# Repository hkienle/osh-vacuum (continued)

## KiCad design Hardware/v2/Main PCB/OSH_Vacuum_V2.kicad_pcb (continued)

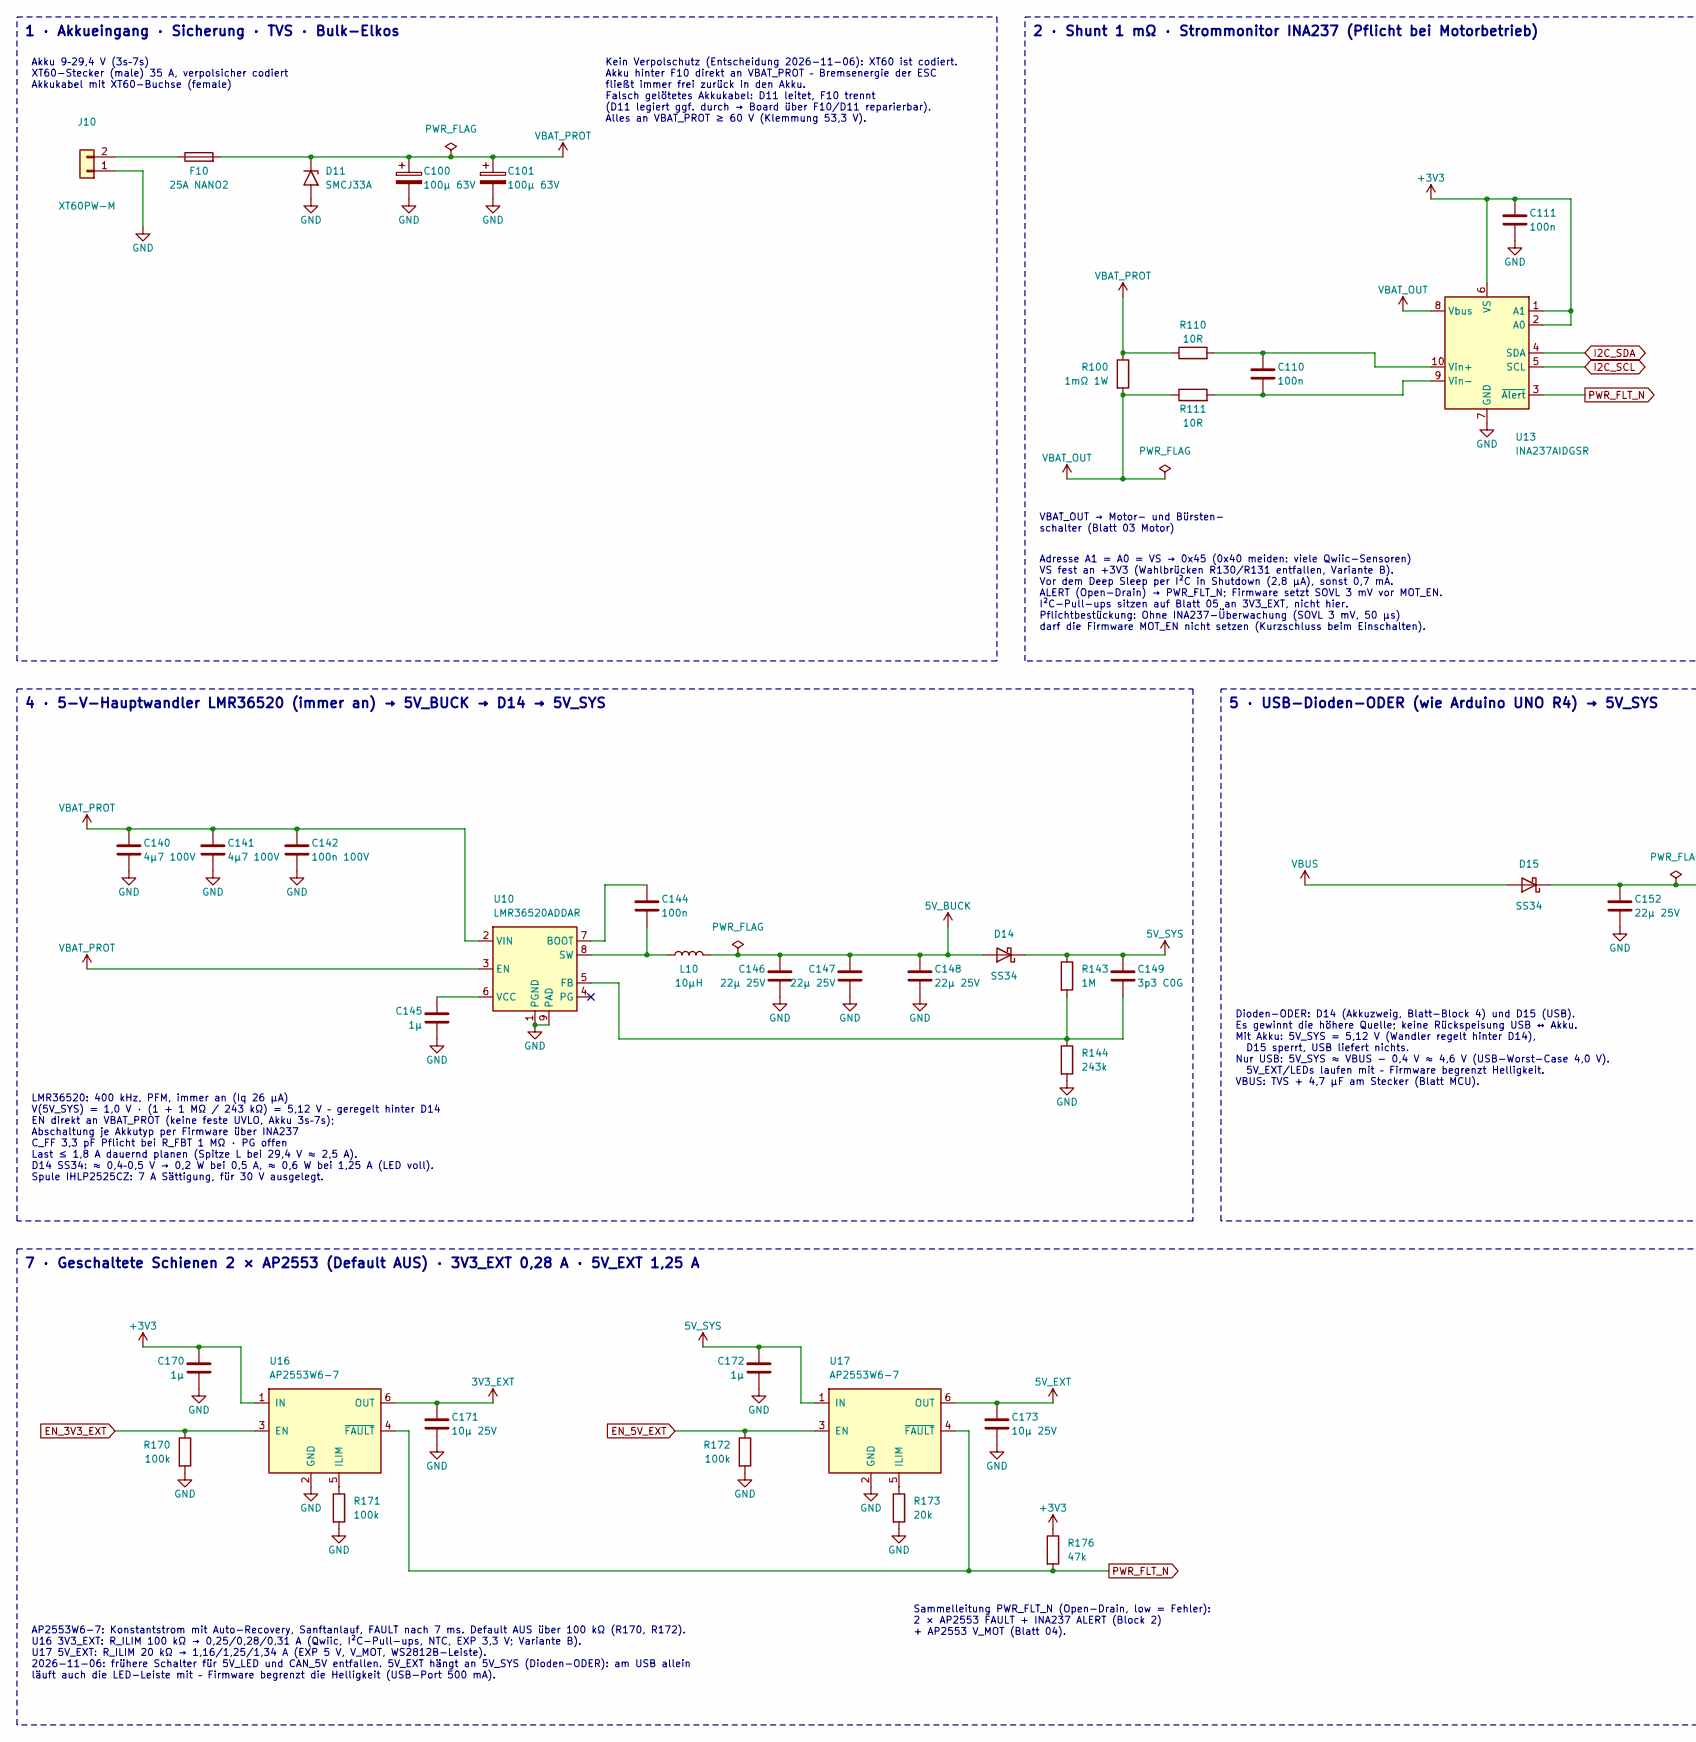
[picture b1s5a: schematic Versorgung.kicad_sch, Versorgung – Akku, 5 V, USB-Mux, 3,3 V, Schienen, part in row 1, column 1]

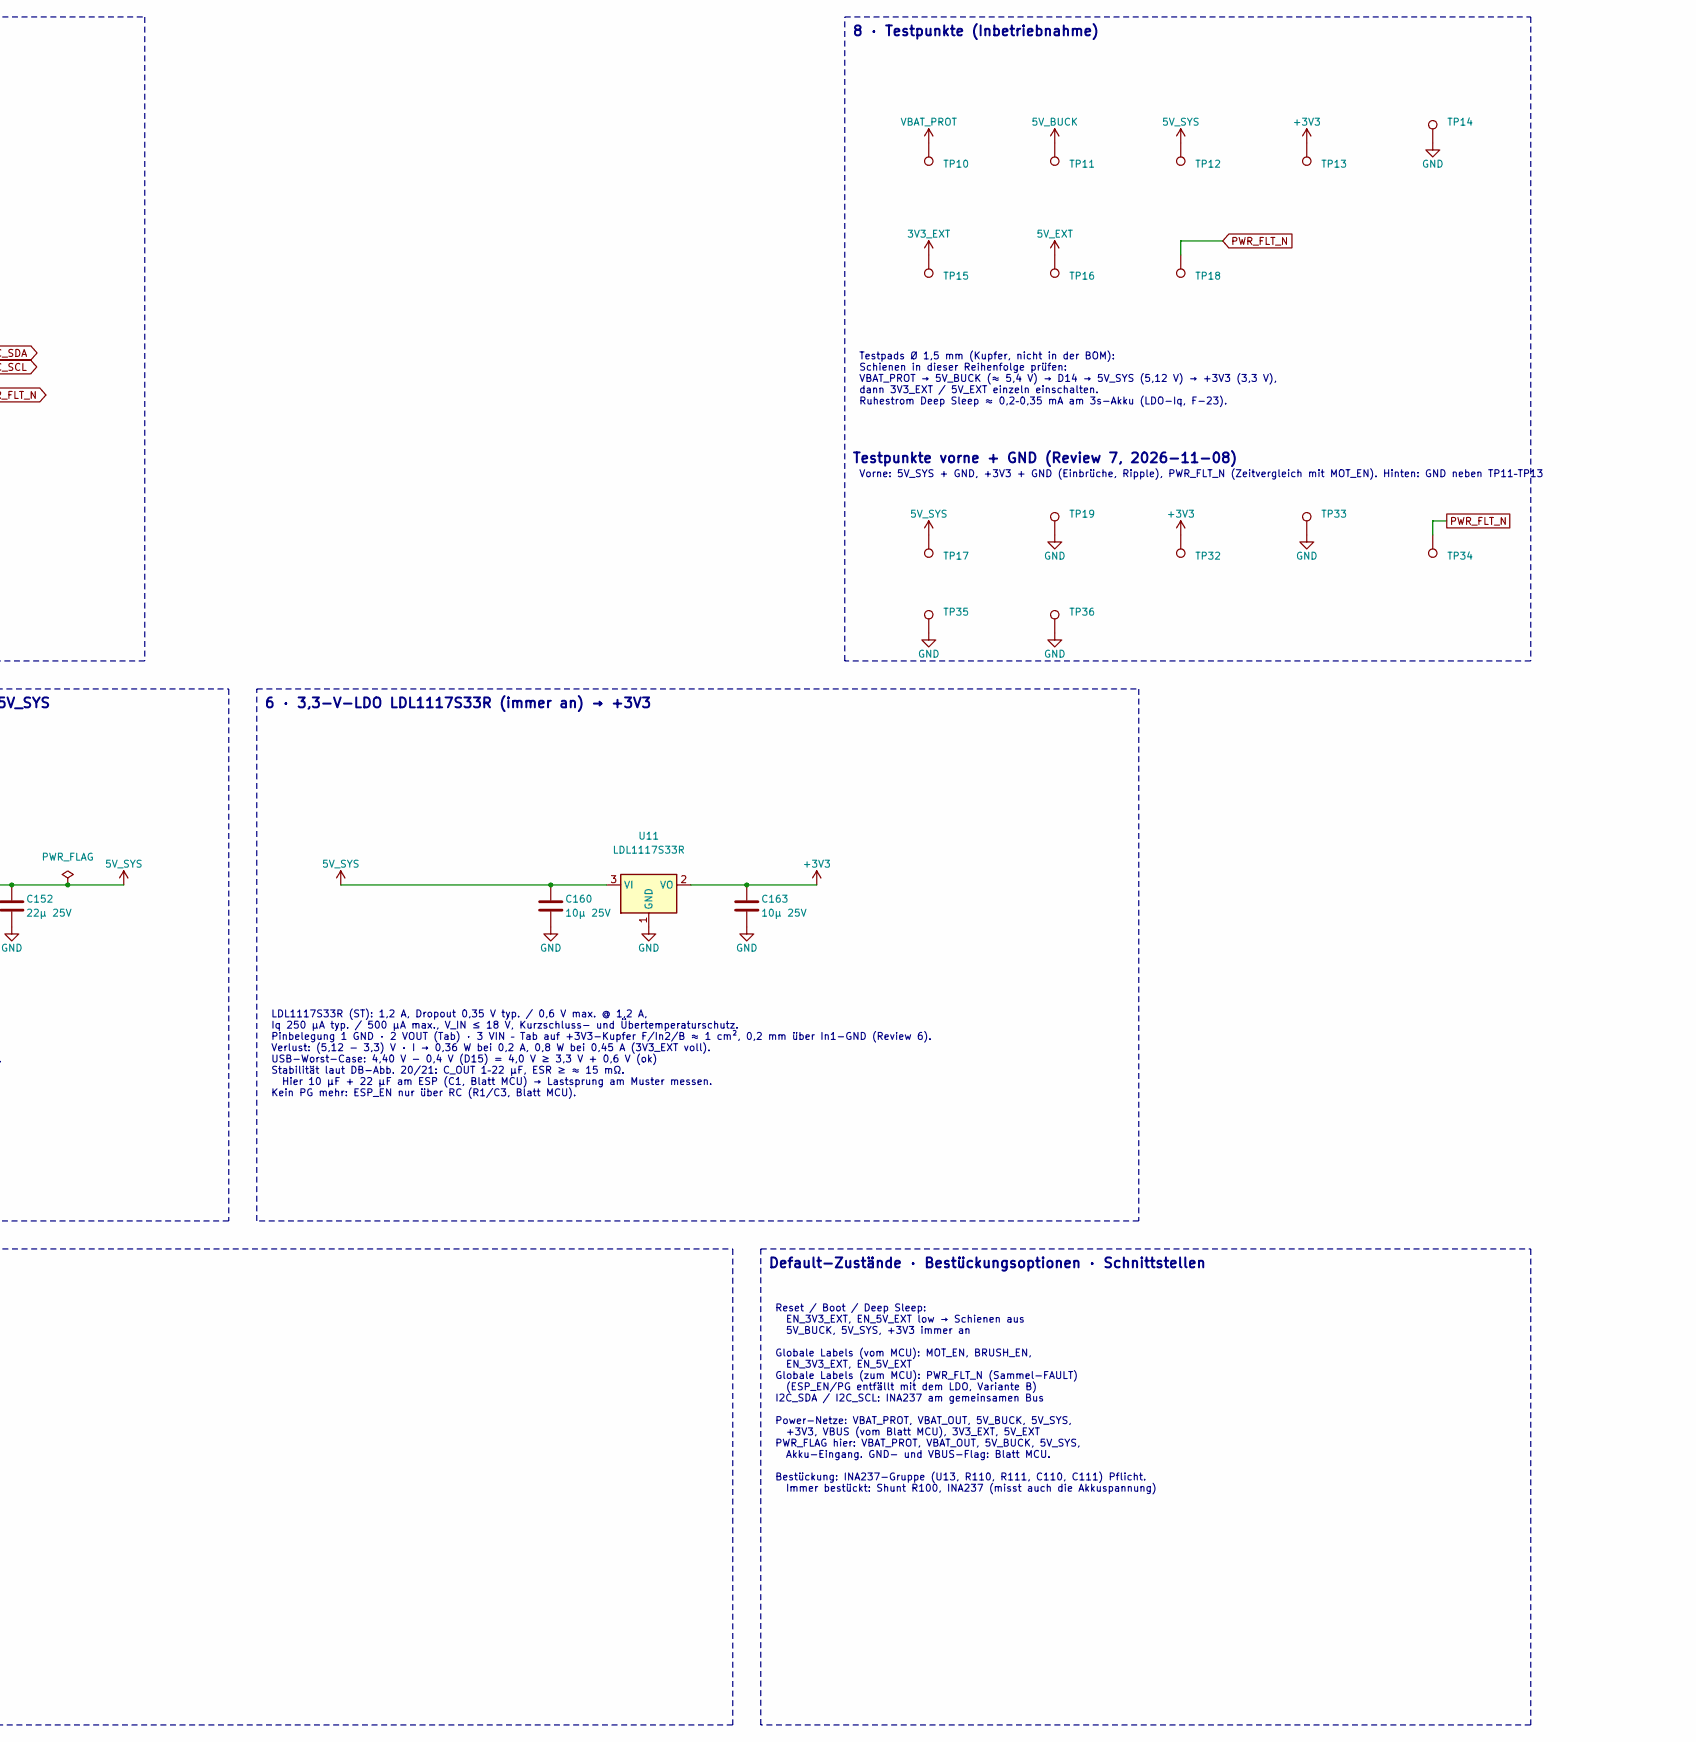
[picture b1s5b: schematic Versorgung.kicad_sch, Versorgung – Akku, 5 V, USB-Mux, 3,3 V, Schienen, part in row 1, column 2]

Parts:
C100, C101: 100µ 63V; CP_Elec_10x10; MPN EEE-FK1J101P; LCSC C128460
C110, C111, C144: 100n; C_0402_1005Metric; MPN CL05B104KO5NNNC; LCSC C1525
C140, C141: 4µ7 100V; C_1210_3225Metric; MPN FS32X475K101EGG; LCSC C381466
C142: 100n 100V; C_0805_2012Metric; MPN CL21B104KCFNNNE; LCSC C28233
C145, C170, C172: 1µ; C_0402_1005Metric; MPN CL05A105KA5NQNC; LCSC C52923
C146, C147, C148: 22µ 25V; C_1206_3216Metric; MPN CL31A226KAHNNNE; LCSC C12891
C149: 3p3 C0G; C_0402_1005Metric; MPN 0402CG3R3C500NT; LCSC C1565
C152: 22µ 25V; C_0805_2012Metric; MPN CL21A226MAQNNNE; LCSC C45783
C160: 10µ 25V; C_0603_1608Metric; MPN CL10A106MA8NRNC; LCSC C96446
C163, C171, C173: 10µ 25V; C_0805_2012Metric; MPN CL21A106KAYNNNE; LCSC C15850
D11: SMCJ33A; D_SMC; MPN SMCJ33A/TR13; LCSC C310047
D14, D15: SS34; D_SMA; MPN SS34; LCSC C8678
F10: 25A NANO2; Fuse_Littelfuse_NANO2-456_20-30A; MPN 0456025.ER; LCSC C315877
J10: XT60PW-M; AMASS_XT60PW-M_1x02_P7.20mm_Horizontal; MPN XT60PW-M; LCSC C98732
L10: 10µH; L_Vishay_IHLP-2525; MPN IHLP2525CZER100M01; LCSC C540965
R100: 1mΩ 1W; R_2512_6332Metric; MPN WSL25121L000FEA18; LCSC C149567
R110, R111: 10R; R_0402_1005Metric; MPN 0402WGF100JTCE; LCSC C25077
R143: 1M; R_0402_1005Metric; MPN 0402WGF1004TCE; LCSC C26083
R144: 243k; R_0402_1005Metric; MPN 0402WGF2433TCE; LCSC C43249
R170, R171, R172: 100k; R_0402_1005Metric; MPN 0402WGF1003TCE; LCSC C25741
R173: 20k; R_0402_1005Metric; MPN 0402WGF2002TCE; LCSC C25765
R176: 47k; R_0402_1005Metric; MPN 0402WGF4702TCE; LCSC C25792
TP10: VBAT_PROT; Testpad_D1.5mm
TP11: 5V_BUCK; Testpad_D1.5mm
TP12: 5V_SYS; Testpad_D1.5mm
TP13: +3V3; Testpad_D1.5mm
TP14, TP35, TP36: GND; Testpad_D1.5mm
TP15: 3V3_EXT; Testpad_D1.5mm
TP16: 5V_EXT; Testpad_D1.5mm
TP17: 5V_SYS; Testpad_D1.0mm
TP18: PWR_FLT_N; Testpad_D1.5mm
TP19, TP33: GND; Testpad_D1.0mm
TP32: +3V3; Testpad_D1.0mm
TP34: PWR_FLT_N; Testpad_D1.0mm
U10: LMR36520ADDAR; SOIC-8-1EP_3.9x4.9mm_P1.27mm_EP2.95x4.9mm_Mask2.71x3.4mm_Th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; MPN LMR36520ADDAR; LCSC C2879422
U11: LDL1117S33R; SOT-223-3_TabPin2; MPN LDL1117S33R; LCSC C435835
U13: INA237AIDGSR; MSOP-10_3x3mm_P0.5mm; MPN INA237AIDGSR; LCSC C2864837
U16, U17: AP2553W6-7; SOT-23-6; MPN AP2553W6-7; LCSC C212302

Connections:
3V3_EXT: C171.1, TP15.1, U16.6 (OUT); also elsewhere on the board
5V_BUCK: C146.1, C147.1, C148.1, D14.2 (A), L10.2, TP11.1
5V_EXT: C173.1, TP16.1, U17.6 (OUT); also elsewhere on the board
5V_SYS: C149.1, C152.1, C160.1, C172.1, D14.1 (K), D15.1 (K), R143.1, TP12.1, TP17.1, U11.3 (VI), U17.1 (IN)
+3V3: C111.1, C163.1, C170.1, R176.1, TP13.1, TP32.1, U11.2 (VO), U13.1 (A1), U13.2 (A0), U13.6 (VS), U16.1 (IN); also elsewhere on the board
EN_3V3_EXT: R170.1, U16.3 (EN); also elsewhere on the board
EN_5V_EXT: R172.1, U17.3 (EN); also elsewhere on the board
GND: C100.2, C101.2, C111.2, C140.2, C141.2, C142.2, C145.2, C146.2, C147.2, C148.2, C152.2, C160.2, C163.2, C170.2, C171.2, C172.2, C173.2, D11.2 (A2), J10.1, R144.2, R170.2, R171.2, R172.2, R173.2, TP14.1, TP19.1, TP33.1, TP35.1, TP36.1, U10.1 (PGND), U10.9 (PAD), U11.1 (GND), U13.7 (GND), U16.2 (GND), U17.2 (GND); also elsewhere on the board
I2C_SCL: U13.5 (SCL); also elsewhere on the board
I2C_SDA: U13.4 (SDA); also elsewhere on the board
unnamed: F10.1, J10.2
unnamed: C144.1, U10.7 (BOOT)
unnamed: C149.2, R143.2, R144.1, U10.5 (FB)
unnamed: C144.2, L10.1, U10.8 (SW)
unnamed: C145.1, U10.6 (VCC)
unnamed: C110.1, R110.2, U13.10 (Vin+)
unnamed: C110.2, R111.2, U13.9 (Vin-)
unnamed: R171.1, U16.5 (ILIM)
unnamed: R173.1, U17.5 (ILIM)
PWR_FLT_N: R176.2, TP18.1, TP34.1, U13.3 (~Alert), U16.4 (~FAULT), U17.4 (~FAULT); also elsewhere on the board
VBAT_OUT: R100.2, R111.1, U13.8 (Vbus); also elsewhere on the board
VBAT_PROT: C100.1, C101.1, C140.1, C141.1, C142.1, D11.1 (A1), F10.2, R100.1, R110.1, TP10.1, U10.2 (VIN), U10.3 (EN)
VBUS: D15.2 (A); also elsewhere on the board

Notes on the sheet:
AP2553W6-7: Konstantstrom mit Auto-Recovery, Sanftanlauf, FAULT nach 7 ms. Default AUS über 100 kΩ (R170, R172). U16 3V3_EXT: R_ILIM 100 kΩ → 0,25/0,28/0,31 A (Qwiic, I²C-Pull-ups, NTC, EXP 3,3 V; Variante B). U17 5V_EXT: R_ILIM 20 kΩ → 1,16/1,25/1,34 A (EXP 5 V, V_MOT, WS2812B-Leiste). 2026-11-06: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
Testpads Ø 1,5 mm (Kupfer, nicht in der BOM): Schienen in dieser Reihenfolge prüfen: VBAT_PROT → 5V_BUCK (≈ 5,4 V) → D14 → 5V_SYS (5,12 V) → +3V3 (3,3 V), dann 3V3_EXT / 5V_EXT einzeln einschalten. Ruhestrom Deep Sleep ≈ 0,2–0,35 mA am 3s-Akku (LDO-Iq, F-23).
VBAT_OUT → Motor- und Bürsten- schalter (Blatt 03 Motor)
Reset / Boot / Deep Sleep: EN_3V3_EXT, EN_5V_EXT low → Schienen aus 5V_BUCK, 5V_SYS, +3V3 immer an Globale Labels (vom MCU): MOT_EN, BRUSH_EN, EN_3V3_EXT, EN_5V_EXT Globale Labels (zum MCU): PWR_FLT_N (Sammel-FAULT) (ESP_EN/PG entfällt mit dem LDO, Variante B) I2C_SDA / I2C_SCL: INA237 am gemeinsam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
1 · Akkueingang · Sicherung · TVS · Bulk-Elkos
LMR36520: 400 kHz, PFM, immer an (Iq 26 µA) V(5V_SYS) = 1,0 V · (1 + 1 MΩ / 243 kΩ) = 5,12 V – geregelt hinter D14 EN direkt an VBAT_PROT (keine feste UVLO, Akku 3s–7s); Abschaltung je Akkutyp per Firmware über INA237 C_FF 3,3 pF Pflicht bei R_FBT 1 MΩ · PG offen Last ≤ 1,8 A dauernd planen (Spitze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
Testpunkte vorne + GND (Review 7, 2026-11-08)
Sammelleitung PWR_FLT_N (Open-Drain, low = Fehler): 2 × AP2553 FAULT + INA237 ALERT (Block 2) + AP2553 V_MOT (Blatt 04).
Kein Verpolschutz (Entscheidung 2026-11-06): XT60 ist codiert. Akku hinter F10 direkt an VBAT_PROT – Bremsenergie der ESC fließt immer frei zurück in den Akku. Falsch gelötetes Akkukabel: D11 leitet, F10 trennt (D11 legiert ggf. durch → Board über F10/D11 reparierbar). Alles an VBAT_PROT ≥ 60 V (Kl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
Default-Zustände · Bestückungsoptionen · Schnittstellen
2 · Shunt 1 mΩ · Strommonitor INA237 (Pflicht bei Motorbetrieb)
7 · Geschaltete Schienen 2 × AP2553 (Default AUS) · 3V3_EXT 0,28 A · 5V_EXT 1,25 A
5 · USB-Dioden-ODER (wie Arduino UNO R4) → 5V_SYS
LDL1117S33R (ST): 1,2 A, Dropout 0,35 V typ. / 0,6 V max. @ 1,2 A, Iq 250 µA typ. / 500 µA max., V_IN ≤ 18 V, Kurzschluss- und Übertemperaturschutz. Pinbelegung 1 GND · 2 VOUT (Tab) · 3 VIN – Tab auf +3V3-Kupfer F/In2/B ≈ 1 cm², 0,2 mm über In1-GND (Review 6). Verlust: (5,12 − 3,3) V · I → 0,36 W b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
8 · Testpunkte (Inbetriebnahme)
6 · 3,3-V-LDO LDL1117S33R (immer an) → +3V3
4 · 5-V-Hauptwandler LMR36520 (immer an) → 5V_BUCK → D14 → 5V_SYS
Dioden-ODER: D14 (Akkuzweig, Blatt-Block 4) und D15 (USB). Es gewinnt die höhere Quelle; keine Rückspeisung USB ↔ Akku. Mit Akku: 5V_SYS = 5,12 V (Wandler regelt hinter D14), D15 sperrt, USB liefert nichts. Nur USB: 5V_SYS ≈ VBUS − 0,4 V ≈ 4,6 V (USB-Worst-Case 4,0 V). 5V_EXT/LEDs laufen mit – Firm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
Adresse A1 = A0 = VS → 0x45 (0x40 meiden: viele Qwiic-Sensoren) VS fest an +3V3 (Wahlbrücken R130/R131 entfallen, Variante B). Vor dem Deep Sleep per I²C in Shutdown (2,8 µA), sonst 0,7 mA. ALERT (Open-Drain) → PWR_FLT_N; Firmware setzt SOVL 3 mV vor MOT_EN. I²C-Pull-ups sitzen auf Blatt 05 an 3V3_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
Akku 9–29,4 V (3s–7s) XT60-Stecker (male) 35 A, verpolsicher codiert Akkukabel mit XT60-Buchse (female)
Vorne: 5V_SYS + GND, +3V3 + GND (Einbrüche, Ripple), PWR_FLT_N (Zeitvergleich mit MOT_EN). Hinten: GND neben TP11–TP13

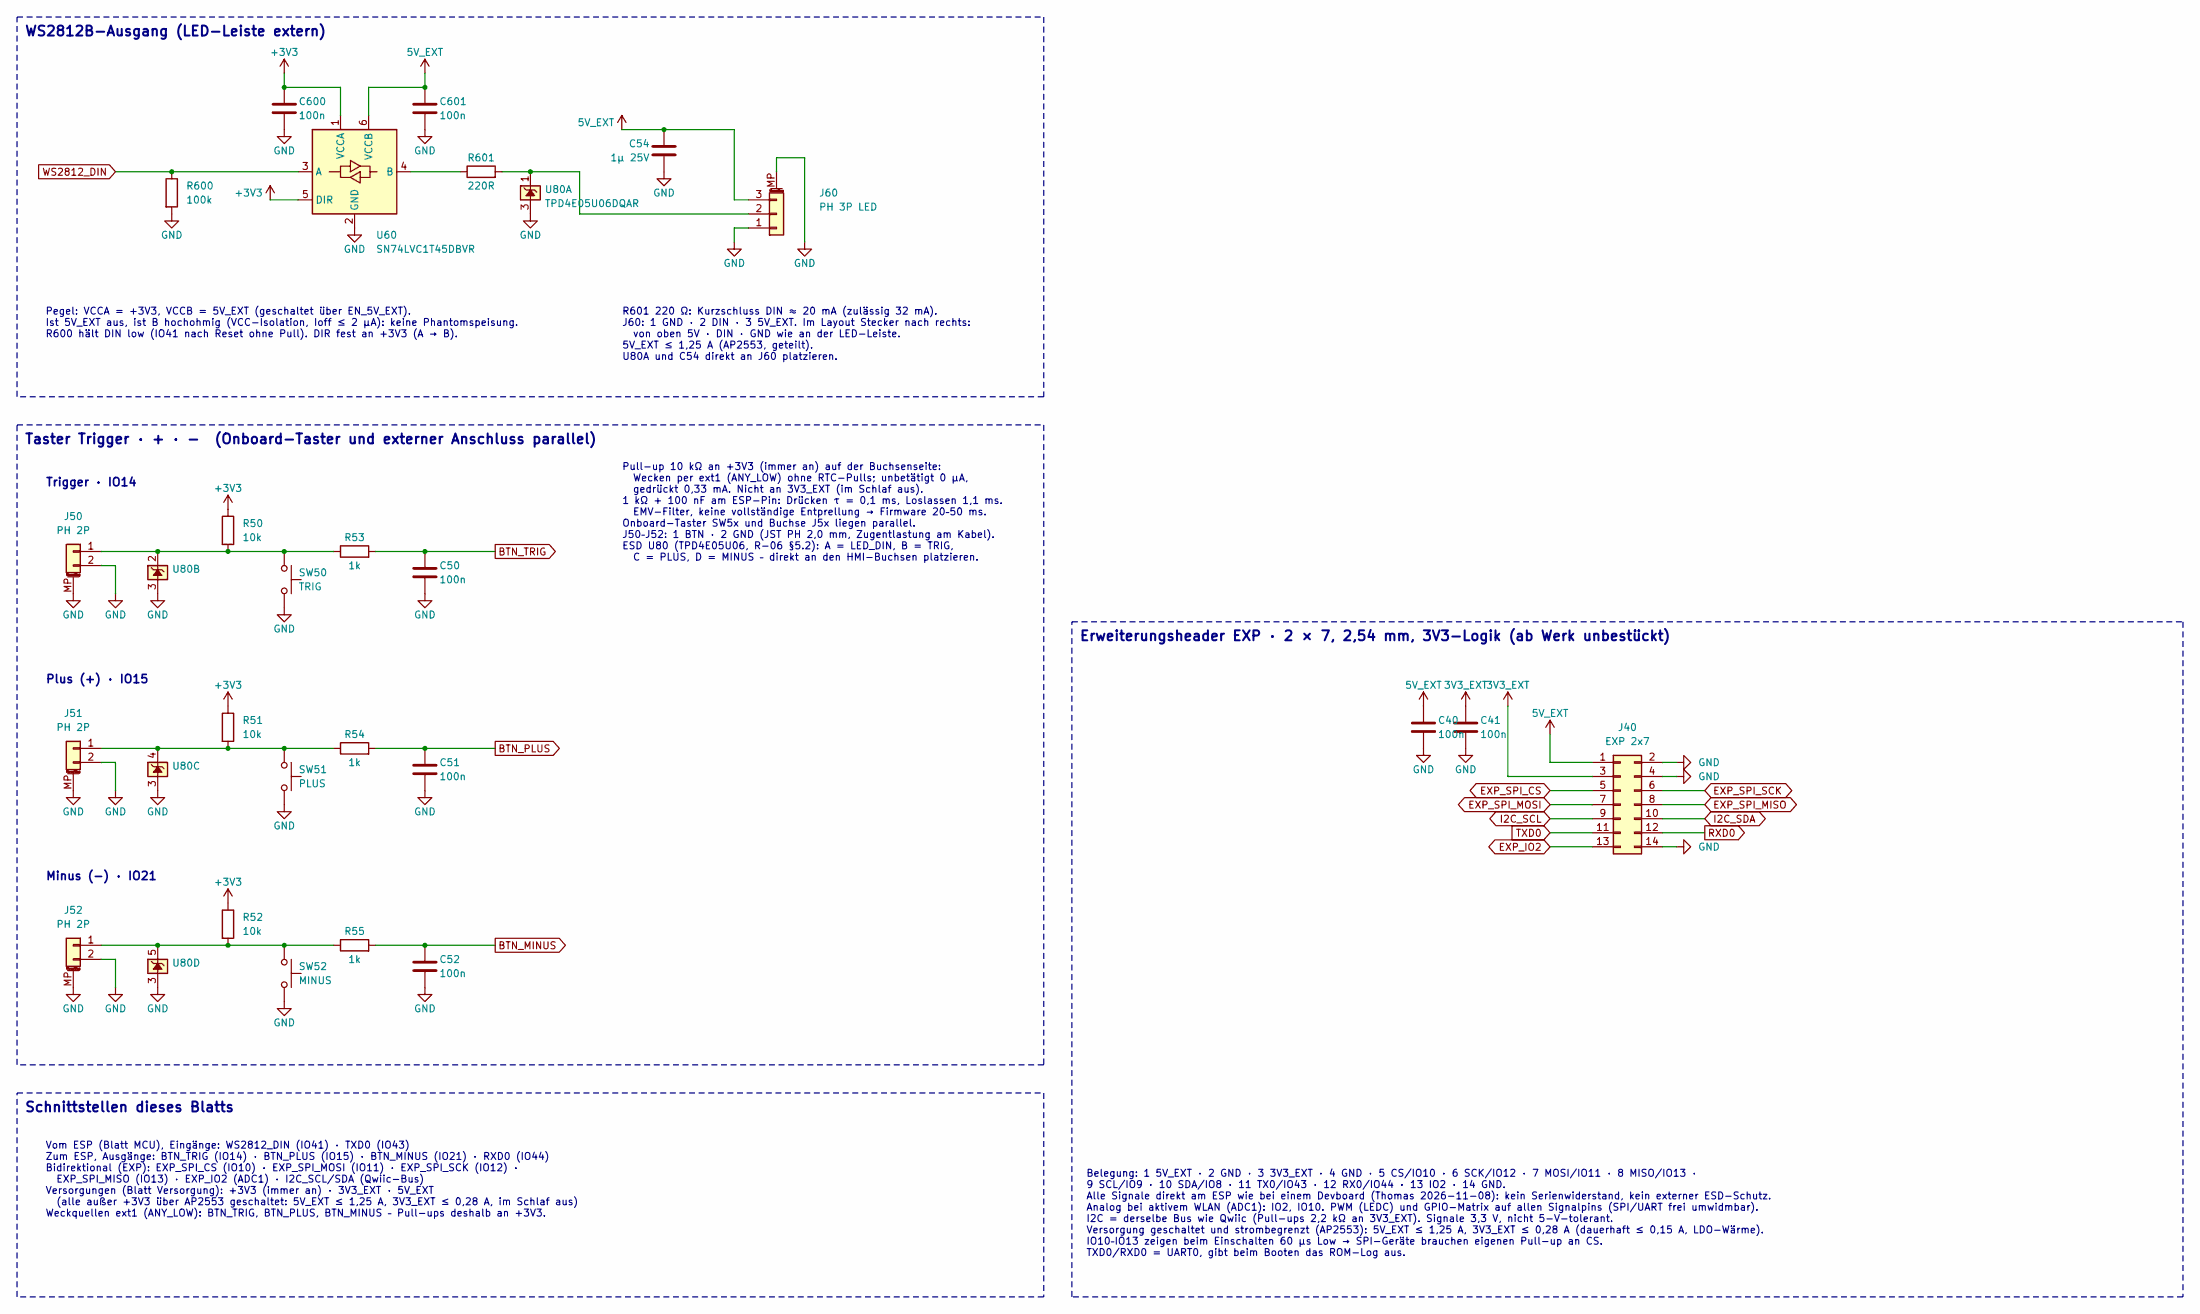
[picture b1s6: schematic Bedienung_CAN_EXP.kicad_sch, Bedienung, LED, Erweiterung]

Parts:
C40, C41, C50, C51, C52, C600, C601: 100n; C_0402_1005Metric; MPN CL05B104KO5NNNC; LCSC C1525
C54: 1µ 25V; C_0402_1005Metric; MPN CL05A105KA5NQNC; LCSC C52923
J40: EXP 2x7; PinHeader_2x07_P2.54mm_Vertical; MPN PZ254V-12-14P; LCSC C492424
J50, J51, J52: PH 2P; JST_PH_S2B-PH-SM4-TB_1x02-1MP_P2.00mm_Horizontal; MPN S2B-PH-SM4-TB(LF)(SN); LCSC C295747
J60: PH 3P LED; JST_PH_S3B-PH-SM4-TB_1x03-1MP_P2.00mm_Horizontal; MPN S3B-PH-SM4-TB(LF)(SN); LCSC C265101
R50, R51, R52: 10k; R_0402_1005Metric; MPN 0402WGF1002TCE; LCSC C25744
R53, R54, R55: 1k; R_0402_1005Metric; MPN 0402WGF1001TCE; LCSC C11702
R600: 100k; R_0402_1005Metric; MPN 0402WGF1003TCE; LCSC C25741
R601: 220R; R_0402_1005Metric; MPN 0402WGF2200TCE; LCSC C25091
SW50: TRIG; SW_SPST_TS-1088-xR020; MPN TS-1088-AR02016; LCSC C720477
SW51: PLUS; SW_SPST_TS-1088-xR020; MPN TS-1088-AR02016; LCSC C720477
SW52: MINUS; SW_SPST_TS-1088-xR020; MPN TS-1088-AR02016; LCSC C720477
U60: SN74LVC1T45DBVR; SOT-23-6; MPN SN74LVC1T45DBVR; LCSC C7843
U80: TPD4E05U06DQAR; USON-10_2.5x1.0mm_P0.5mm; MPN TPD4E05U06DQAR; LCSC C138714

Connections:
3V3_EXT: C41.1, J40.3; also elsewhere on the board
5V_EXT: C40.1, C54.1, C601.1, J40.1, J60.3, U60.6 (VCCB); also elsewhere on the board
+3V3: C600.1, R50.1, R51.1, R52.1, U60.1 (VCCA), U60.5 (DIR); also elsewhere on the board
BTN_MINUS: C52.1, R55.2; also elsewhere on the board
BTN_PLUS: C51.1, R54.2; also elsewhere on the board
BTN_TRIG: C50.1, R53.2; also elsewhere on the board
EXP_IO2: J40.13; also elsewhere on the board
EXP_SPI_CS: J40.5; also elsewhere on the board
EXP_SPI_MISO: J40.8; also elsewhere on the board
EXP_SPI_MOSI: J40.7; also elsewhere on the board
EXP_SPI_SCK: J40.6; also elsewhere on the board
GND: C40.2, C41.2, C50.2, C51.2, C52.2, C54.2, C600.2, C601.2, J40.2, J40.4, J40.14, J50.2, J50.MP (MountPin), J51.2, J51.MP (MountPin), J52.2, J52.MP (MountPin), J60.1, J60.MP (MountPin), R600.2, SW50.2, SW51.2, SW52.2, U60.2 (GND), U80.3 (GND), U80.8 (GND); also elsewhere on the board
I2C_SCL: J40.9; also elsewhere on the board
I2C_SDA: J40.10; also elsewhere on the board
unnamed: J50.1, R50.2, R53.1, SW50.1, U80.2 (D1-)
unnamed: J51.1, R51.2, R54.1, SW51.1, U80.4 (D2+)
unnamed: J52.1, R52.2, R55.1, SW52.1, U80.5 (D2-)
unnamed: J60.2, R601.2, U80.1 (D1+)
unnamed: R601.1, U60.4 (B)
RXD0: J40.12; also elsewhere on the board
TXD0: J40.11; also elsewhere on the board
WS2812_DIN: R600.1, U60.3 (A); also elsewhere on the board

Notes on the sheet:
Plus (+) · IO15
Schnittstellen dieses Blatts
Minus (−) · IO21
WS2812B-Ausgang (LED-Leiste extern)
Taster Trigger · + · − (Onboard-Taster und externer Anschluss parallel)
Trigger · IO14
Vom ESP (Blatt MCU), Eingänge: WS2812_DIN (IO41) · TXD0 (IO43) Zum ESP, Ausgänge: BTN_TRIG (IO14) · BTN_PLUS (IO15) · BTN_MINUS (IO21) · RXD0 (IO44) Bidirektional (EXP): EXP_SPI_CS (IO10) · EXP_SPI_MOSI (IO11) · EXP_SPI_SCK (IO12) · EXP_SPI_MISO (IO13) · EXP_IO2 (ADC1) · I2C_SCL/SDA (Qwiic-Bus) Ver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
Erweiterungsheader EXP · 2 × 7, 2,54 mm, 3V3-Logik (ab Werk unbestückt)
R601 220 Ω: Kurzschluss DIN ≈ 20 mA (zulässig 32 mA). J60: 1 GND · 2 DIN · 3 5V_EXT. Im Layout Stecker nach rechts: von oben 5V · DIN · GND wie an der LED-Leiste. 5V_EXT ≤ 1,25 A (AP2553, geteilt). U80A und C54 direkt an J60 platzieren.
Belegung: 1 5V_EXT · 2 GND · 3 3V3_EXT · 4 GND · 5 CS/IO10 · 6 SCK/IO12 · 7 MOSI/IO11 · 8 MISO/IO13 · 9 SCL/IO9 · 10 SDA/IO8 · 11 TX0/IO43 · 12 RX0/IO44 · 13 IO2 · 14 GND. Alle Signale direkt am ESP wie bei einem Devboard (Thomas 2026-11-08): kein Serienwiderstand, kein externer ESD-Schutz. Analog 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
Pull-up 10 kΩ an +3V3 (immer an) auf der Buchsenseite: Wecken per ext1 (ANY_LOW) ohne RTC-Pulls; unbetätigt 0 µA, gedrückt 0,33 mA. Nicht an 3V3_EXT (im Schlaf aus). 1 kΩ + 100 nF am ESP-Pin: Drücken τ = 0,1 ms, Loslassen 1,1 ms. EMV-Filter, keine vollständige Entprellung → Firmware 20–50 ms. Onboa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
Pegel: VCCA = +3V3, VCCB = 5V_EXT (geschaltet über EN_5V_EXT). Ist 5V_EXT aus, ist B hochohmig (VCC-Isolation, Ioff ≤ 2 µA): keine Phantomspeisung. R600 hält DIN low (IO41 nach Reset ohne Pull). DIR fest an +3V3 (A → B).

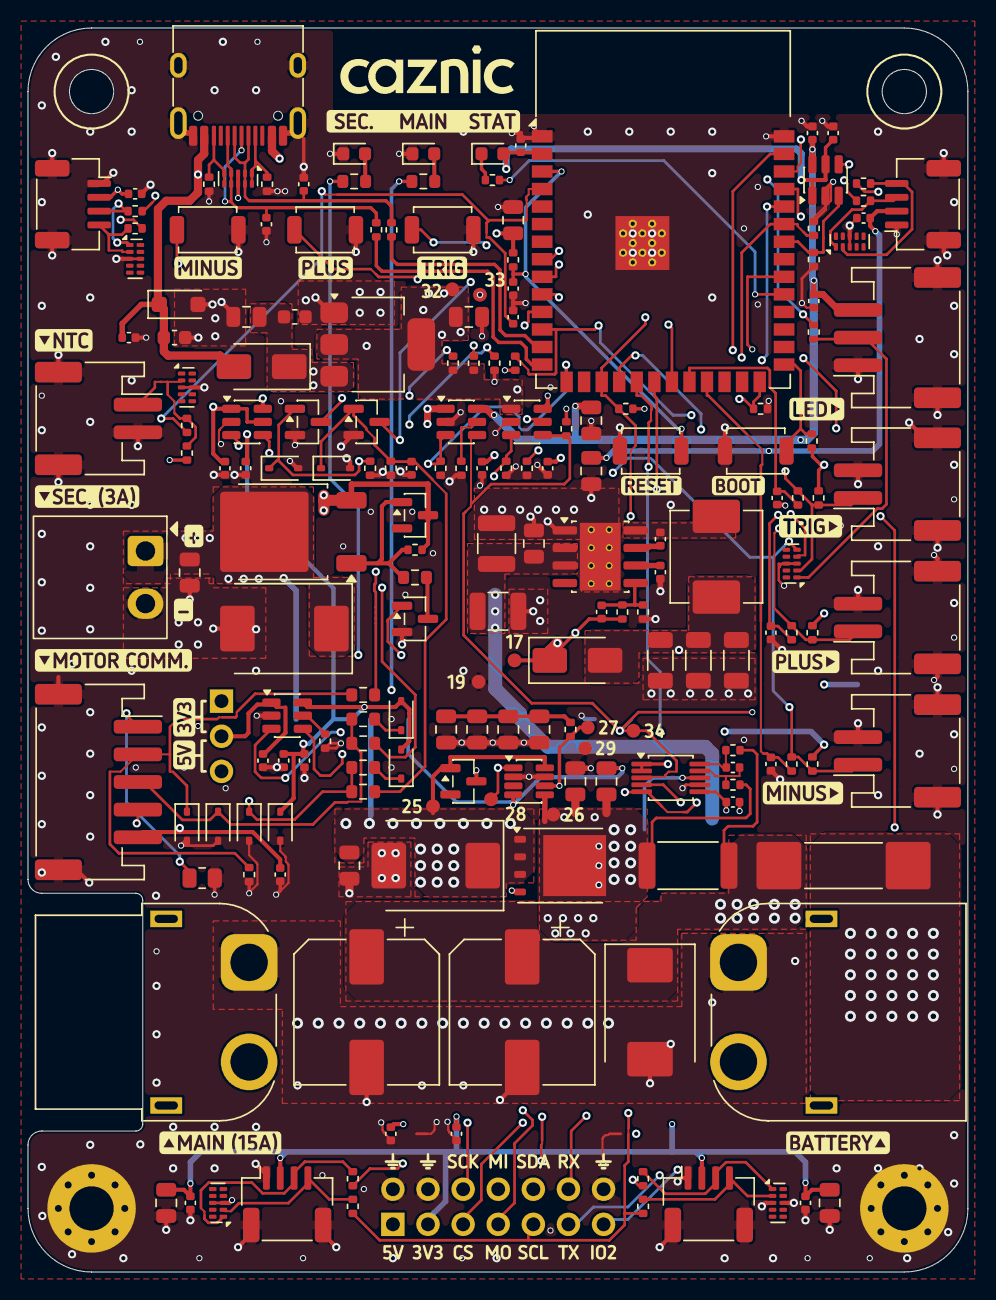
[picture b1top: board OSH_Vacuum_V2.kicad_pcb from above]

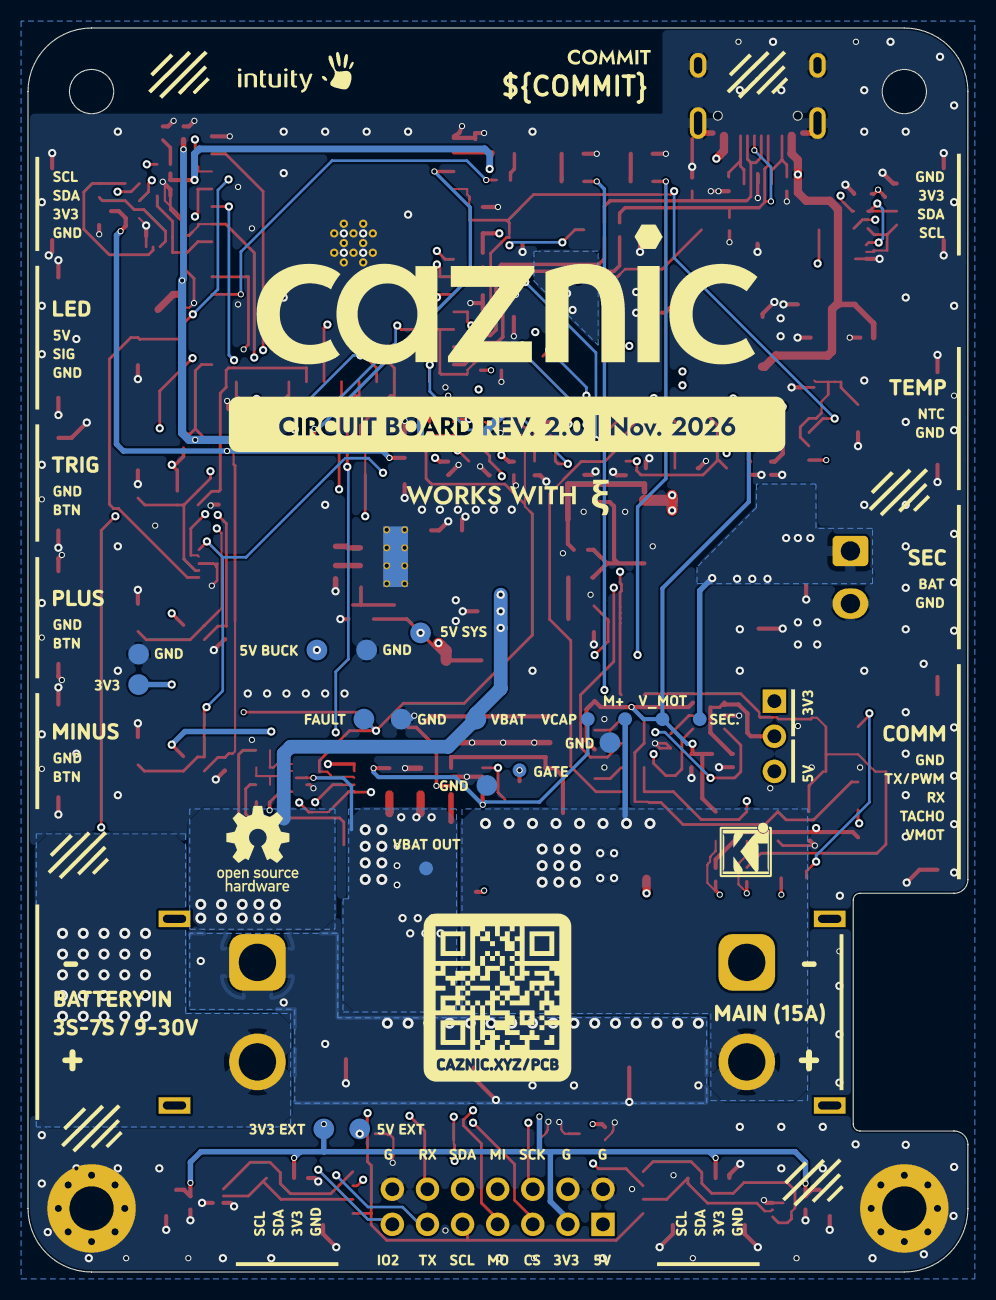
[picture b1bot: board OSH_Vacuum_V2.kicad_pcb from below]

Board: 4 copper layers, 68.0 x 90.0 mm, 210 parts (18 on the bottom side), 85 nets.

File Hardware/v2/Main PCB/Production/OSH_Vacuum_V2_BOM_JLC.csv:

Comment,Designator,Footprint,LCSC Part #
1k,"R10,R53,R54,R55,R57",R_0402_1005Metric,C11702
V_MOT-Wahl,JP60,PinHeader_1x03_P2.54mm_Vertical,C124376
100u 63V,"C100,C101",CP_Elec_10x10,C128460
22u 25V,"C146,C147,C148",C_1206_3216Metric,C12891
TPD4E05U06DQAR,"U2,U80,U81,U82,U83,U84,U85",USON-10_2.5x1.0mm_P0.5mm,C138714
1mR 1W,R100,R_2512_6332Metric,C149567
100n,"C110,C111,C144,C2,C40,C41,C50,C51,C52,C53,C600,C601,C607,C608,C609,C611,C8",C_0402_1005Metric,C1525
3p3 C0G,C149,C_0402_1005Metric,C1565
10u 25V,"C163,C171,C173,C624,C625",C_0805_2012Metric,C15850
USB-C 16P,J1,USB_C_Receptacle_HRO_TYPE-C-31-M-12,C165948
10R 0805,R617,R_0805_2012Metric,C17415
SMF5.0A,D3,D_SOD-123F,C193402
4u7 16V,C7,C_0603_1608Metric,C19666
MMBT3904,"Q60,Q61",SOT-23,C20526
1k,"R22,R30",R_0603_1608Metric,C21190
AP2553W6-7,"U16,U17,U62",SOT-23-6,C212302
1N4148WS,"D61,D63,D66,D67",D_SOD-323,C2128
weiss STAT,"D2,D23,D28",LED_0603_1608Metric,C2290
10R,"R110,R111",R_0402_1005Metric,C25077
220R,R601,R_0402_1005Metric,C25091
22R,"R5,R6,R620,R621,R622,R623,R624,R625,R626,R627",R_0402_1005Metric,C25092
100k,"R170,R171,R172,R600,R604,R605,R607",R_0402_1005Metric,C25741
10k,"R1,R15,R17,R2,R50,R51,R52,R56,R611,R615",R_0402_1005Metric,C25744
20k,R173,R_0402_1005Metric,C25765
47k,"R176,R28,R610,R614",R_0402_1005Metric,C25792
10k,"R29,R606,R608,R612",R_0603_1608Metric,C25804
47k 0603,"R609,R613",R_0603_1608Metric,C25819
2k2,"R21,R660,R661",R_0402_1005Metric,C25879
5k1,"R3,R4",R_0402_1005Metric,C25905
1M,R143,R_0402_1005Metric,C26083
PH 3P LED,J60,JST_PH_S3B-PH-SM4-TB_1x03-1MP_P2.00mm_Horizontal,C265101
MOTOR-SIG,J61,JST_PH_S5B-PH-SM4-TB_1x05-1MP_P2.00mm_Horizontal,C265104
100n 100V,"C142,C20,C21,C22,C23,C26,C29,C30,C31",C_0805_2012Metric,C28233
BZX84-B12,"D21,D26",SOT-23,C282540
HYG025N06LS1C2,Q20,TDSON-8-1,C2827231
INA237AIDGSR,U13,MSOP-10_3x3mm_P0.5mm,C2864837
LMR36520ADDAR,U10,SOIC-8-1EP_3.9x4.9mm_P1.27mm_EP2.95x4.9mm_Mask2.71x3.4mm_ThermalVias,C2879422
ESP32-S3-WROOM-1-N16R8,U1,ESP32-S3-WROOM-1,C2913202
PH 2P,"J50,J51,J52,J53",JST_PH_S2B-PH-SM4-TB_1x02-1MP_P2.00mm_Horizontal,C295747
SMCJ33A,D11,D_SMC,C310047
25A NANO2,F10,Fuse_Littelfuse_NANO2-456_20-30A,C315877
LM74502DDFR,U20,TSOT-23-8,C3236215
AOD409,Q24,TO-252-2,C36220
4u7 100V,"C140,C141",C_1210_3225Metric,C381466
BUERSTE,J22,DORABO_DB2ERC-3.81-2P_P3.81mm_Horizontal,C395684
XT60PW-F,J20,AMASS_XT60PW-F_1x02_P7.20mm_Horizontal,C428722
243k,R144,R_0402_1005Metric,C43249
LDL1117S33R,U11,SOT-223-3_TabPin2,C435835
22u 25V,"C1,C152",C_0805_2012Metric,C45783
EXP 2x7,J40,PinHeader_2x07_P2.54mm_Vertical,C492424
SD36C,"D60,D62,D64,D65",D_SOD-323,C502537
1u,"C145,C170,C172,C3,C54,C605,C606,C620,C621,C622,C623",C_0402_1005Metric,C52923
10uH,L10,L_Vishay_IHLP-2525,C540965
RESET,"SW1,SW2,SW50,SW51,SW52",SW_SPST_TS-1088-xR020,C720477
Qwiic QT1,"J62,J63,J64,J65",Megastar_ZX-SH1.0-4PWT_1x04-1MP_P1.00mm_Horizontal,C7430446
SN74LVC1T45DBVR,"U60,U63",SOT-23-6,C7843
B560C,"D22,D27",D_SMC,C85100
2N7002,Q25,SOT-23,C8545
SS34,"D14,D15",D_SMA,C8678
10u 25V,C160,C_0603_1608Metric,C96446
XT60PW-M,J10,AMASS_XT60PW-M_1x02_P7.20mm_Horizontal,C98732

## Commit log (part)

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2025-11-27 Added KiCad and manufacturing files for the benchtop PCB V1.0
2025-12-15 Added firmware
2025-12-15 Updated readme files
2026-04-15 Display integration, highly functional update.
2026-04-15 Updat readme
2026-04-20 add printed parts
2026-04-20 moved printfiles into correct dir
2026-04-21 added mesh part for the cyclone
2026-04-21 Updated Core skrew layout
2026-04-21 Added Holes for different skrew length in lid
2026-04-27 added flat nozzle variants
2026-04-27 renamed files to match BOM
2026-04-27 added Checklist for build overview
2026-04-27 added landing page
2026-04-27 Refactor index.html for VAC V1.x, replacing old styles and scripts with new ones, and updating the structure for the print checklist. Removed outdated checklist assets and added new functionality for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
2026-04-27 Update BOM metadata handling and add new part number validation features. Removed obsolete bom-meta.js file and integrated new part number schema checks and placeholder inference in bom-meta.ts. Upda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
2026-04-27 Add filtering options for mass and time in the workshop interface, update BOM metadata for purchased parts, and enhance rendering logic for purchased items.
2026-04-27 Enhance workshop interface with mass and time filtering inputs, update asset paths for deployment, and improve error handling in GitHub file fetching.
2026-04-27 Update asset paths in index.html and build/index.html, remove obsolete CSS and JS files, and enhance rendering logic with field suggestion datalists for improved user experience in the workshop inter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
2026-04-28 Enhance landing page with 3D background rendering, update styles for improved UI, and add new project documentation links. Introduce new GLTF model for visual representation and optimize button inter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
2026-04-28 Update Vite dependency metadata with new hash values for improved build integrity.
2026-04-28 Refactor asset management in index.html and build/index.html, update script and stylesheet paths, remove obsolete files, and enhance error handling in GitHub file fetching. Introduce new CSS and JS f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
2026-04-29 Remove PlatformIO auto-generated VSCode files from tracking
2026-04-29 Integrate maximum stats functionality into firmware. Updated display and button handling to support new settings for maximum duty, LED themes, and telemetry. Enhanced LED behavior for OTA updates and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
2026-04-29 First variant of a UART controller.
2026-04-30 added cart and wallmount, moved nozzle to new aux folder
2026-04-30 made the cable channel bigger
2026-04-30 Converting step to stl files
    Converting .step to .stl files via python script using FreeCADCmd command line tool. Requires freecadcmd to be installed and in the PATH of your shell.
2026-05-05 removed cable divider in the bottom to avoid pinching
2026-05-05 added .stl files for each .step file
    As my printer does not support .step and Mac finder allows preview of .stl I added them in the same folder structure.
2026-05-05 added hose adapter
2026-05-13 Add BOM for vacuum component assembly
    Added a Bill of Materials (BOM) for vacuum component assembly, including printed parts, metal hardware, and additional parts with procurement details.
2026-05-22 Change motor behaviour
2026-06-18 switch to 1.5 inch display
2026-06-19 add display sim to the project
2026-06-19 Refactor documentation for MAC build setup and display architecture. Improved formatting for clarity and consistency across tables, enhancing readability of build status, UI components, and related f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
2026-06-19 new hosted webUI for bluetooth connection
2026-06-23 Add Mac build setup notes and PlatformIO IDE recommendations
2026-06-24 Add data overview and roadmap for floor detection
2026-06-24 Add data overview and roadmap for floor detection (#13)
2026-06-26 Update floor detection roadmap
2026-06-26 Update floor detection roadmap (#14)
